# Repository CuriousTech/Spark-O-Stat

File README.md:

## Spark-O-Stat
SparkCore based WiFi thermostat project

Note: As of 2/18/2016 the SparkCore code is depreciated.  The Photon is now in use, and all changes will be made there.  A new large font has been added since there's more room, and data is published instead of read.  The HTML page and .js scripts will not work with the old code.

This is my first GitHib project, and the idea is simple.  It's opensource and flexible with a color LCD touchscreen, rotary encoder and speaker to allow room for creative software.  The initial concept will be to control for efficiency by scaling the indoor temperature to outdoor instead of drastic bumps using schedules, and adjustments using predictive code based on experiment and observation.  But all that can be removed and replaced with schedules if desired.

A periodic screenshot of data collection: This is sometime in the summer.  The orange temp is in another room.  Unfortunately the thermostat gets the most sun in the house, so it's the most erratic.   I've noticed the AC doesn't run at the low and high points of the day as it used to.  That was unexpected.  And the electric bill was down about 30% most of this year.  

This is the older desktop control running on PngMagic  

More info at http://www.curioustech.net/curiousprojects.html

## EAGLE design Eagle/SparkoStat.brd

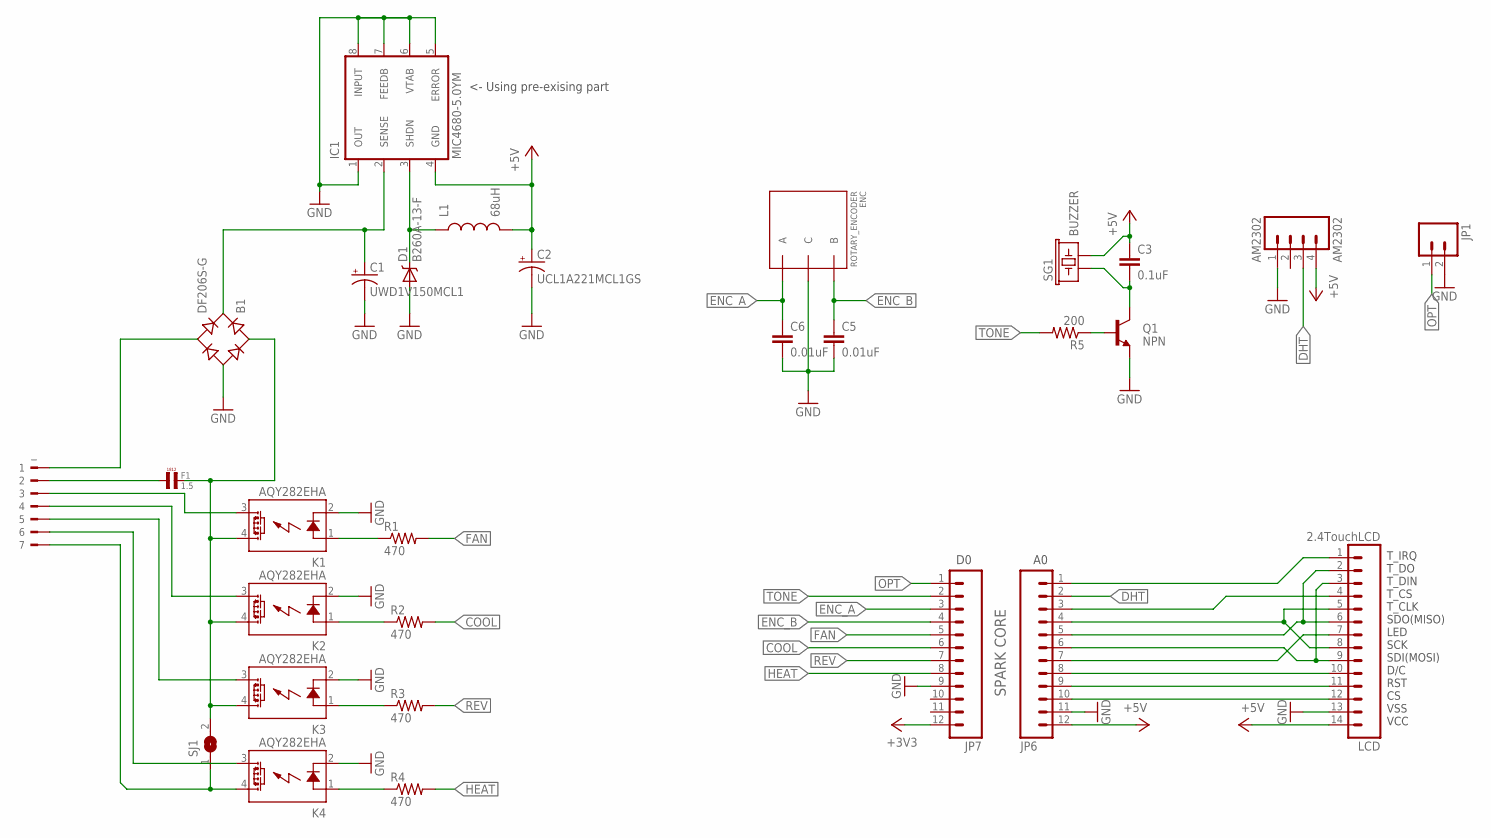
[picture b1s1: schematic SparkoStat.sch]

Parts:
AM2302: AM2302; 1X04
B1: DF206S-G; DFS
C1: UWD1V150MCL1; PANASONIC_C
C2: UCL1A221MCL1GS; PANASONIC_D
C3: 0.1uF; 0805
C5, C6: 0.01uF; 0805
D1: B260A-13-F; SMA-DIODE
ENC: ROTARY_ENCODER; ROTORY_ENC
F1: 1.5; L4,8
IC1: MIC4680-5.0YM; SO-08
JP1: M02PTH; 1X02
JP6, JP7: M12LOCK; 1X12_LOCK
K1, K2, K3, K4: AQY282EHA; SOP04
L1: 68uH; DR1030
LCD: 2.4TouchLCD; 1X14_LOCK
Q1: NPN; SOT23
R1, R2, R3, R4: 470; 0805
R5: 200; 0805
SG1: BUZZER; BUZZER-12MM-NS
SJ1: SJ
_: 180-7

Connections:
+3V3: JP7.12
+5V: AM2302.4, C2.+, C3.1, IC1.4 (GND), JP6.12, L1.2, LCD.14, SG1.- (2)
COOL: JP7.6, R2.2
DHT: AM2302.3, JP6.2
ENC_A: C6.1, ENC.A, JP7.3
ENC_B: C5.1, ENC.B, JP7.4
FAN: JP7.5, R1.2
GND: AM2302.1, B1.-, C1.-, C2.-, C5.2, C6.2, D1.A, ENC.C, IC1.1 (OUT), IC1.5 (ERROR), IC1.6 (VTAB), IC1.7 (FEEDB), IC1.8 (INPUT), JP1.2, JP6.11, JP7.9, K1.2 (K), K2.2 (K), K3.2 (K), K4.2 (K), LCD.13, Q1.2 (E)
HEAT: JP7.8, R4.2
unnamed: JP6.1, LCD.1
unnamed: D1.C, IC1.3 (SHDN), L1.1
unnamed: K4.3 (DS2), _.6
unnamed: K1.1 (A), R1.1
unnamed: K2.1 (A), R2.1
unnamed: B1.AC1, F1.P$2 (2), K1.4 (DS1), K2.4 (DS1), K3.4 (DS1), SJ1.2
unnamed: K3.1 (A), R3.1
unnamed: K4.1 (A), R4.1
unnamed: K2.3 (DS2), _.4
unnamed: K1.3 (DS2), _.3
unnamed: B1.AC2, _.1
unnamed: JP6.6, LCD.3, LCD.9
unnamed: JP6.5, LCD.2, LCD.6
unnamed: B1.+, C1.+, IC1.2 (SENSE)
unnamed: JP6.9, LCD.11
unnamed: JP6.10, LCD.12
unnamed: JP6.8, LCD.10
unnamed: JP6.4, LCD.5, LCD.8
unnamed: K3.3 (DS2), _.5
unnamed: JP6.7, LCD.7
unnamed: F1.P$1 (1), _.2
unnamed: C3.2, Q1.3 (C), SG1.+ (1)
unnamed: JP6.3, LCD.4
unnamed: K4.4 (DS1), SJ1.1, _.7
unnamed: Q1.1 (B), R5.1
OPT: JP1.1, JP7.1
REV: JP7.7, R3.2
TONE: JP7.2, R5.2

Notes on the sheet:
SPARK CORE
T_IRQ T_DO T_DIN T_CS T_CLK SDO(MISO) LED SCK SDI(MOSI) D/C RST CS VSS VCC
<- Using pre-exising part

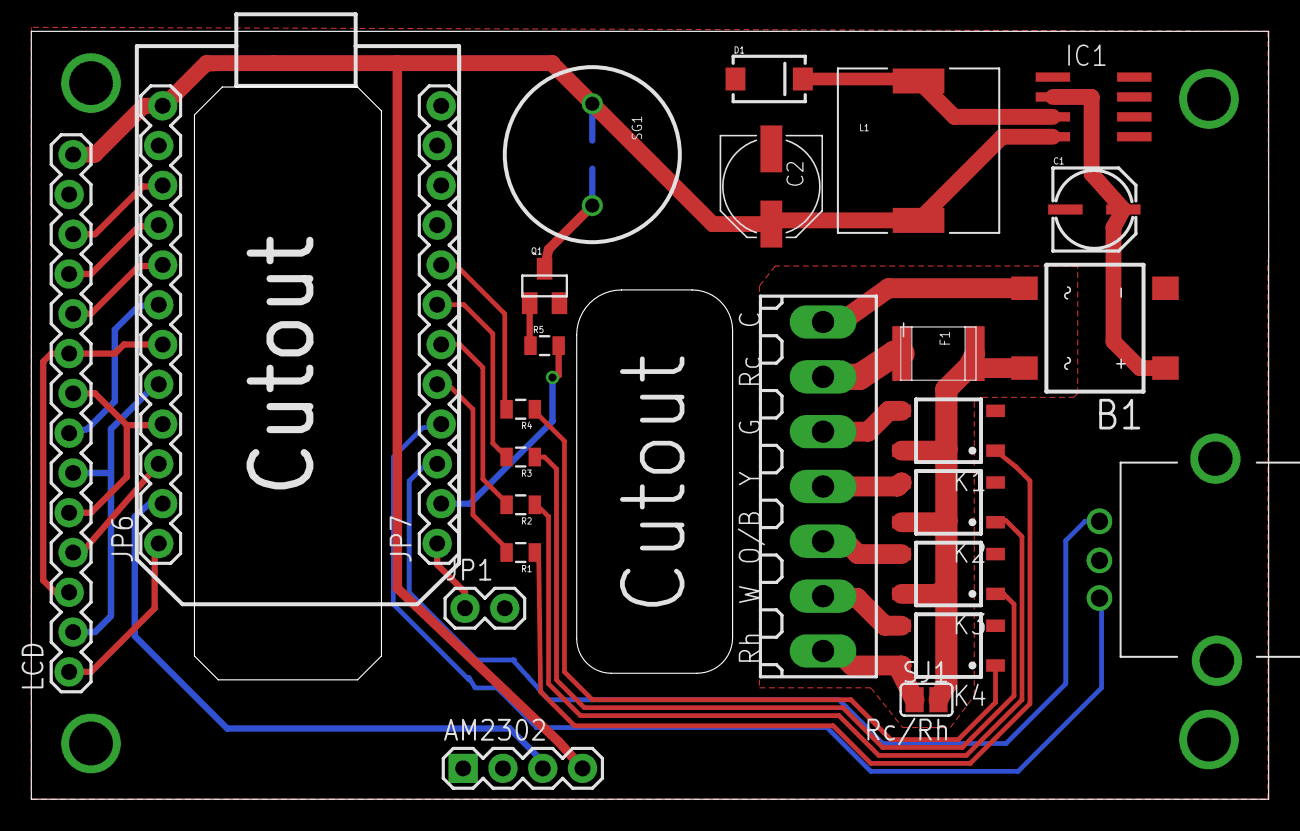
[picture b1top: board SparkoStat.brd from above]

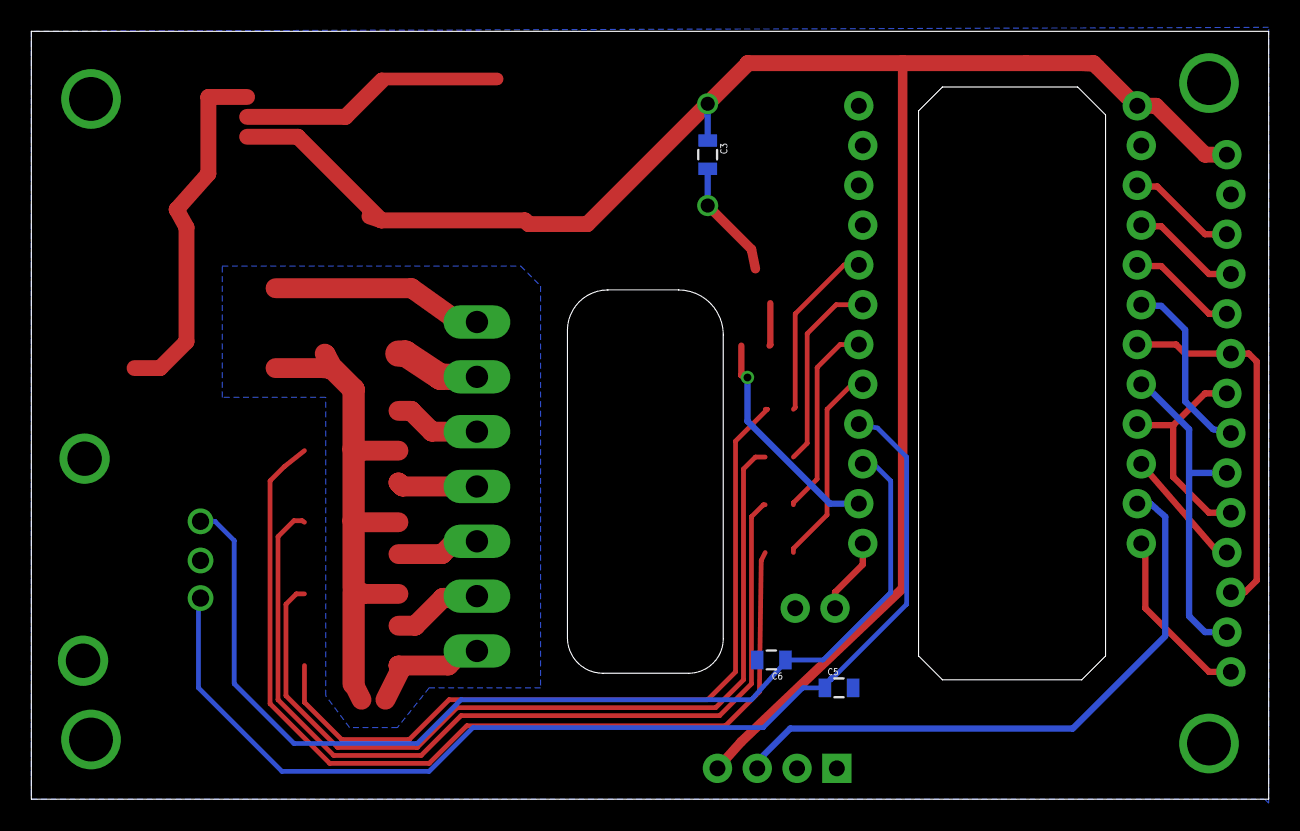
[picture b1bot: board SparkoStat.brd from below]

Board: 2 copper layers, 79.0 x 49.0 mm, 29 parts (3 on the bottom side), 36 nets.

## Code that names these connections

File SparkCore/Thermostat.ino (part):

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int8_t  dispNote = -1;

const char  *pszHvacFan[] = {"Auto", " On "};
const char  *pszHvacMode[] = {"Off ", "Cool", "Heat", "Auto"};
const char  *pszHeatMode[] = {" HP ", " NG ", "Auto"};

// convert n*10 to XXX.X with neg
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void DrawButtons()
{
    const char szLabels[3][4] = {"Out", "In", "Rh"};
    const char szLabels2[3][6] = {"Fan", "Mode", "Heat"};
    int8_t i;

    tft.setTextColor(ILI9341_YELLOW, ILI9341_BLACK);
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
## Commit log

2015-01-26 Create thermostat.ino
    Main Spark Core code
2015-01-26 Create HVAC.h
    Header for HVAC library. HVAC pins defined here.
2015-01-26 Create HVAC.cpp
    HVAC library.
2015-01-26 Create Encoder.h
    Rotary encoder library header, Encoder class def.
2015-01-26 Create Encoder.cpp
    Simple rotory encoder class. Interrupt or poll.
2015-01-26 Create UTouch.h
    Touchscreen library header.
2015-01-26 Create UTouch.cpp
    Touchscreen library by Henning Karlsen modded for Spark Core
2015-01-26 Create XMLParser.h
    XML Reader/parser for Spark Core
2015-01-26 Create XMLParser.cpp
    XML parser with callback for weather forecast
2015-01-26 Create XMLReader.h
    XML reader header
2015-01-26 Create XMLReader.cpp
    XMLReader class for SparkCore. Specific to weather.gov forecast.
2015-01-26 Create SparkoStat.sch
    Eagle schematic
2015-01-26 Create SparkoStat.brd
    Eagle board layout
2015-01-26 Create SparkRemote.js
    Windows script for controlling and monitoring thermostat
2015-01-27 Tabs and error checking added
2015-01-28 Concatinated more vars
2015-01-29 Figured out folders!
2015-02-24 Fixing tabs
2015-04-04 Fixed updatePeaks
2015-04-16 autoMode heatMode fix
2015-05-28 Auto heatmode, particle.io update
2015-05-28 Adding auto heat mode option
2015-07-28 Cleaning up after sim
2015-07-28 Heatpump solenoid was reversed, sim in ifdef
2015-07-28 Add override button
2015-07-30 Added RH to settings query
2015-07-31 Added RH display and some cleanup
2015-08-02 A little cleanup and fixes
2015-08-02 Not crazy but fully functional.
2015-08-03 Added override cancel
2015-08-03 Found more bugs
2015-08-07 Changed override to delta offset
2015-08-07 Update HVAC.cpp
    Change override to delta
    heatpump switch while running fix
2015-08-07 Refresh from build
2015-08-12 Add forecast shifting
2015-08-12 Swapped target and threshold
2015-08-27 Changed DHT22 to verticle
2015-08-27 Rolled back to previous before fcshift
2015-09-18 Moved a var to public
2015-09-18 Add publish event for mode, run, fan change
2015-09-18 Added event stream
2015-10-08 filter counter now minutes
2015-10-08 Winter is coming.
2015-10-08 Log.mode reports simple HP/NG for cycle
2015-10-13 Added remote temperature control
2015-10-13 Added cancel to remote temperature control
2015-10-16 Using new EEPROM.get/put
2015-10-16 Added simulated fan state for furnace override
2015-10-24 Particle stream listener for SparkRemote
2015-10-28 Changed to jquery
2015-11-18 Forecast status publishing
2015-11-18 Changed filter counter
2015-11-27 Tab bug in github
2015-12-08 Fixed override cancel
2015-12-08 Changed to semi-auto mode
2015-12-17 Split fan post time for HP/cool
2015-12-17 Enabled multithreading
2016-01-16 Sort of radio button style
2016-01-25 Ensure outputs are off at startup for safety
2016-01-31 Fan was stopping when fanMode = on after cycle
2016-01-31 Better auto-reconnect, using 0.4.9 firmware
2016-02-18 New version for event stream/Photon
2016-03-13 Fixed clock display

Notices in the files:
parts and their libraries:
SparkFun-Connectors: Licensing: CC v3.0 Share-Alike You are welcome to use this library for commercial purposes.
